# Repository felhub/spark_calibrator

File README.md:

# spark_calibrator
## Be carefull! Igntion coils can step up the voltage up to 1:100, wich means on the secondary side there can be voltages up to 40kV!
Over serial communication controlled spark generator using an arduino as digital controller and a car ignition coil as step up transformer.  
A 3D modell of the full assembly and spark gab, as well as all 3d printed parts will be added soon.

## Schematics (without Arduino)
A MOSFET is used to switch the coil. To avoid voltage spikes on the direct switching action, C2 is used to buffer the spike.  
To limit the overall voltage spike on the primary side, the TVS-diode D2 is used to limit to 440V.  

Switching and digital side are isolated via an optocoupler

## Simulation

In blue one can see the input pwm signal, triggering the charge of the coil, seen in the current over the coil in red. After voltage to the coil is cut of, the magnetic field collapses with a huge voltage spike in green. The spike is limited by the TVS-diode to 440V, this can be seen as clipping on the green signal.

## Board layout
The board can be screwed directly to the coil terminals, to keep the leads as short as possible, depending on your could the board has to be adjusted.  
The Arduino is mounted via a 3D printed part on the back of the coil and connects to the board via 3 wires.  

| main_board | ignition coil |
|:-----------------------------:|:----------------------------------:|
|  |  |

## Spark gap

In order to generate consistent sparks, the spark gap should consist of two pointy metal parts. For spark calibration, audio reflections should be avoided, therefore I build a small spark gap device, using sewing needles and cardboard. The width can be varied, to test the effect of the spark length on the generated impulse.

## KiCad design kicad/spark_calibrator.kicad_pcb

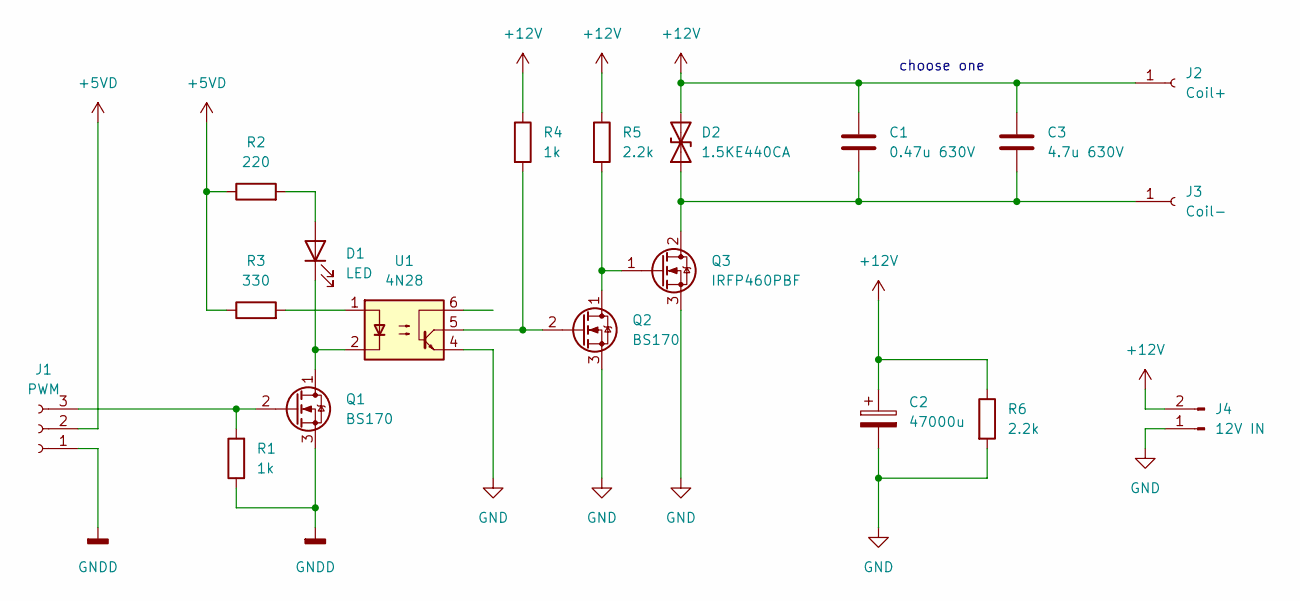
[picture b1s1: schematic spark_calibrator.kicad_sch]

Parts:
C1: 0.47u 630V; C_Rect_L26.5mm_W10.5mm_P22.50mm_MKS4
C2: 47000u; CP_Radial_D35.0mm_P10.00mm_SnapIn
C3: 4.7u 630V; C_Rect_L31.5mm_W17.0mm_P27.50mm_MKS4
D1: LED; LED_D3.0mm
D2: 1.5KE440CA; D_DO-201_P15.24mm_Horizontal
J1: PWM; PinHeader_1x03_P2.54mm_Horizontal
J2: Coil+; MountingHole_6.4mm_M6_Pad
J3: Coil-; MountingHole_5.3mm_M5_Pad
J4: 12V IN; TerminalBlock_bornier-2_P5.08mm
Q1, Q2: BS170; TO-92_Inline
Q3: IRFP460PBF; TO-247-3_Vertical
R1, R4: 1k; R_Axial_DIN0207_L6.3mm_D2.5mm_P10.16mm_Horizontal
R2: 220; R_Axial_DIN0207_L6.3mm_D2.5mm_P10.16mm_Horizontal
R3: 330; R_Axial_DIN0207_L6.3mm_D2.5mm_P10.16mm_Horizontal
R5, R6: 2.2k; R_Axial_DIN0207_L6.3mm_D2.5mm_P10.16mm_Horizontal
U1: 4N28; DIP-6_W7.62mm

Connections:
+5VD: J1.2, R2.1, R3.1
+12V: C1.1, C2.1, C3.1, D2.2 (A2), J2.1, J4.2, R4.1, R5.1, R6.1
GND: C2.2, J4.1, Q2.3 (S), Q3.3 (S), R6.2, U1.4
GNDD: J1.1, Q1.3 (S), R1.1
unnamed: C1.2, C3.2, D2.1 (A1), J3.1, Q3.2 (D)
unnamed: D1.1 (K), Q1.1 (D), U1.2
unnamed: D1.2 (A), R2.2
unnamed: J1.3, Q1.2 (G), R1.2
unnamed: Q2.1 (D), Q3.1 (G), R5.2
unnamed: Q2.2 (G), R4.2, U1.5
unnamed: R3.2, U1.1

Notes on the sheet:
choose one

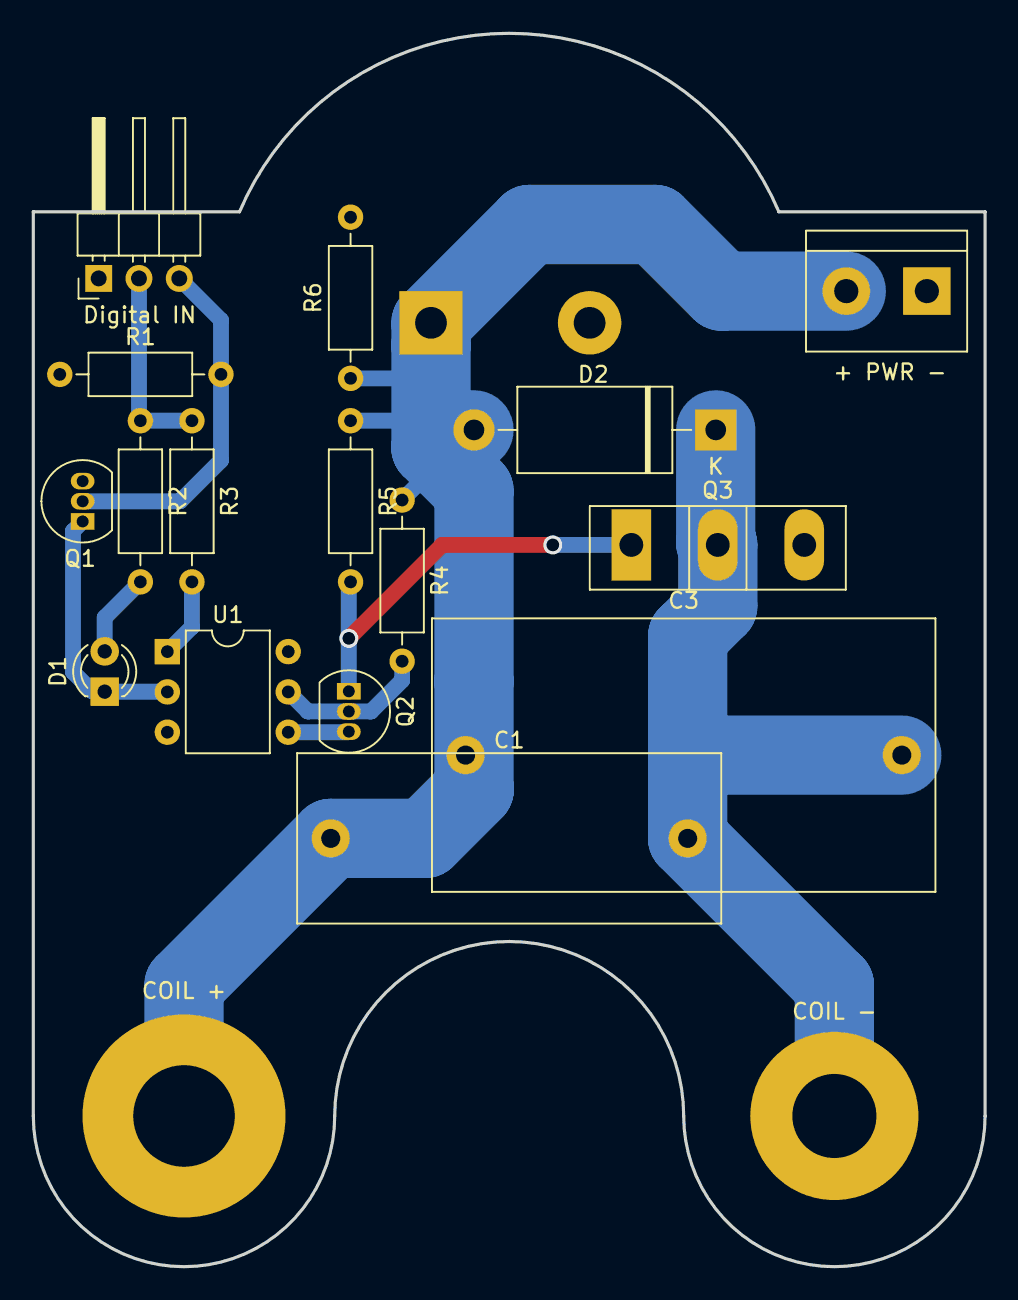
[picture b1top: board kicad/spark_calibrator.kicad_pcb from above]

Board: 2 copper layers, 60.0 x 77.8 mm, 19 parts (1 on the bottom side), 11 nets.

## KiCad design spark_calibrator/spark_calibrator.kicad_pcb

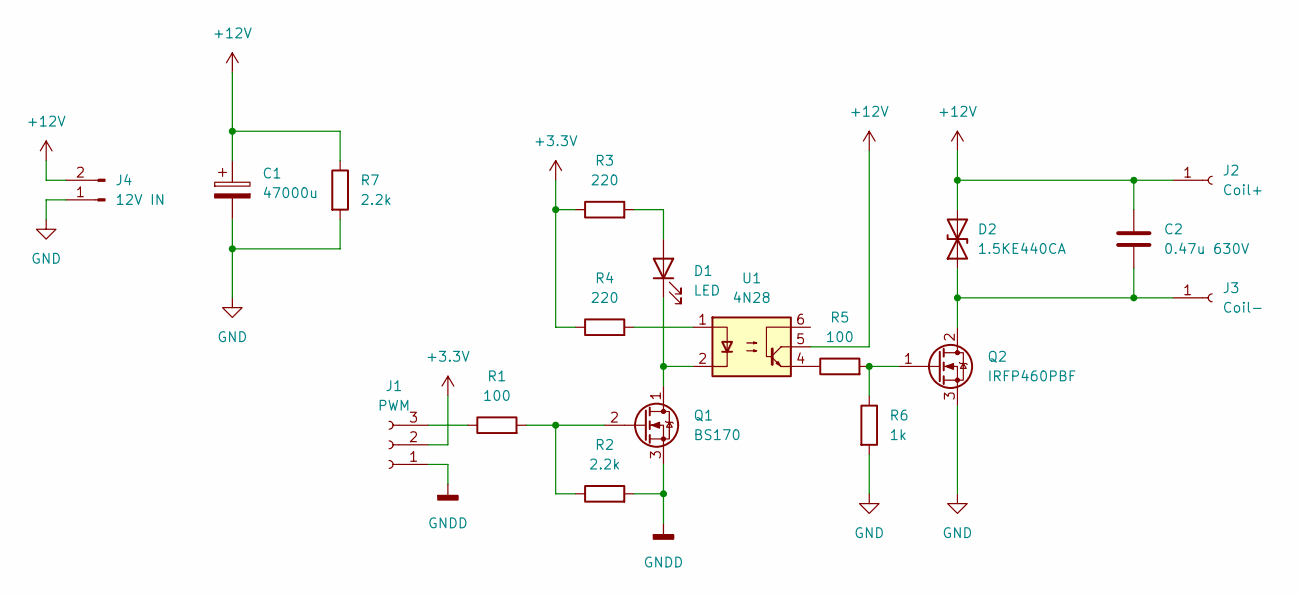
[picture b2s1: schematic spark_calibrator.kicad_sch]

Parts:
C1: 47000u; CP_Radial_D35.0mm_P10.00mm_SnapIn
C2: 0.47u 630V; C_Rect_L26.5mm_W10.5mm_P22.50mm_MKS4
D1: LED; LED_D3.0mm
D2: 1.5KE440CA; D_DO-201_P15.24mm_Horizontal
J1: PWM; PinHeader_1x03_P2.54mm_Horizontal
J2: Coil+; MountingHole_6.4mm_M6_Pad
J3: Coil-; MountingHole_5.3mm_M5_Pad
J4: 12V IN; TerminalBlock_bornier-2_P5.08mm
Q1: BS170; TO-92_Inline
Q2: IRFP460PBF; TO-247-3_Vertical
R1, R5: 100; R_Axial_DIN0207_L6.3mm_D2.5mm_P10.16mm_Horizontal
R2, R7: 2.2k; R_Axial_DIN0207_L6.3mm_D2.5mm_P10.16mm_Horizontal
R3, R4: 220; R_Axial_DIN0207_L6.3mm_D2.5mm_P10.16mm_Horizontal
R6: 1k; R_Axial_DIN0207_L6.3mm_D2.5mm_P10.16mm_Horizontal
U1: 4N28; DIP-6_W7.62mm

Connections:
+3V3: J1.2, R3.1, R4.1
+12V: C1.1, C2.1, D2.2 (A2), J2.1, J4.2, R7.1, U1.5
GND: C1.2, J4.1, Q2.3 (S), R6.2, R7.2
GNDD: J1.1, Q1.3 (S), R2.2
unnamed: C2.2, D2.1 (A1), J3.1, Q2.2 (D)
unnamed: D1.1 (K), Q1.1 (D), U1.2
unnamed: D1.2 (A), R3.2
unnamed: J1.3, R1.1
unnamed: Q1.2 (G), R1.2, R2.1
unnamed: Q2.1 (G), R5.2, R6.1
unnamed: R4.2, U1.1
unnamed: R5.1, U1.4

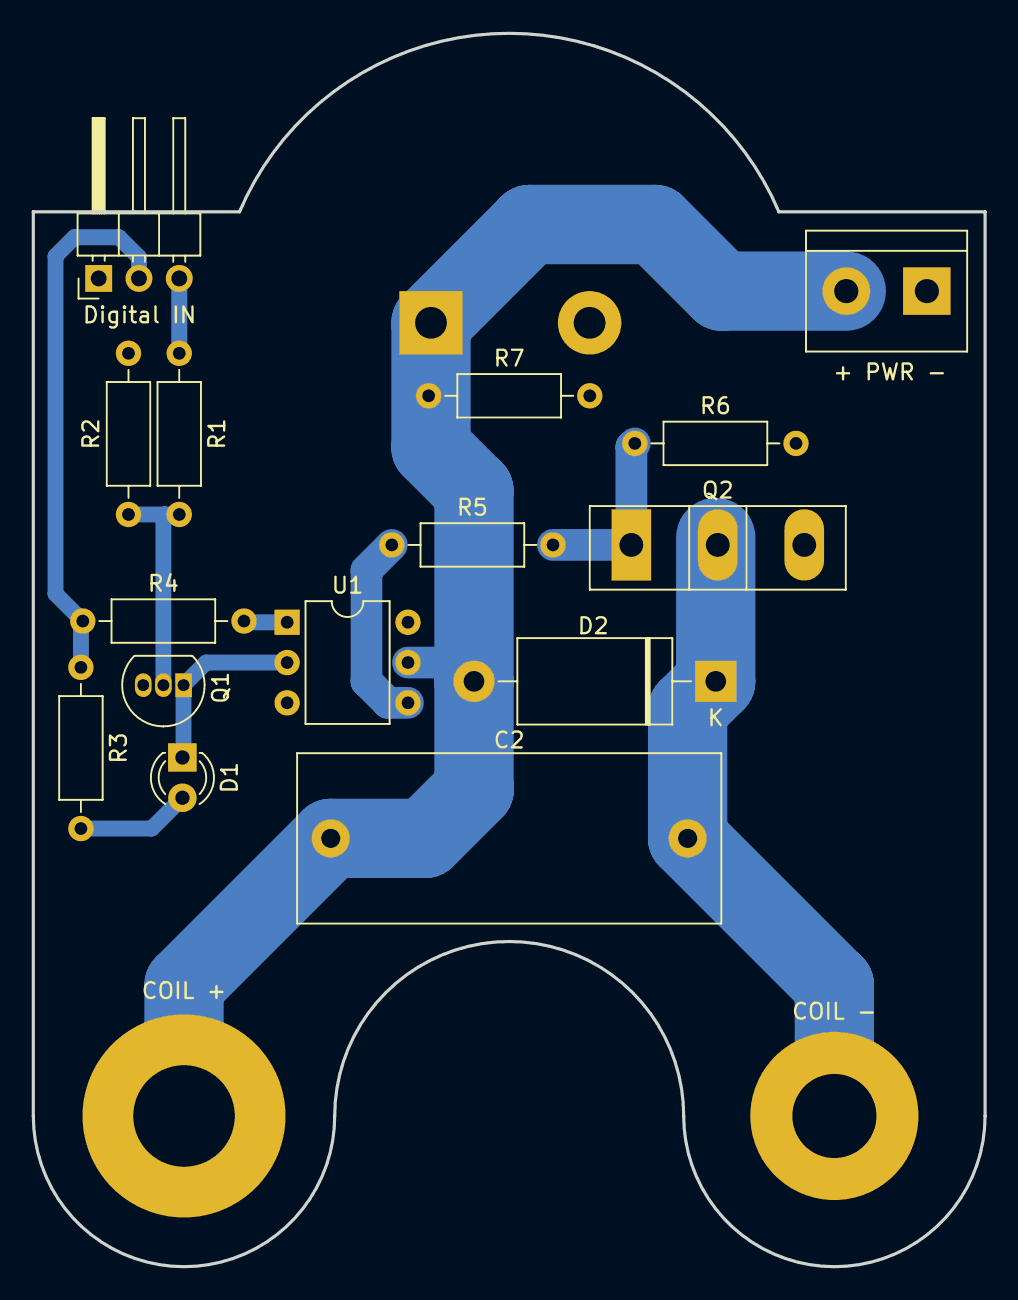
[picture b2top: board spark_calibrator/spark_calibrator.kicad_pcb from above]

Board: 2 copper layers, 60.0 x 77.8 mm, 18 parts (1 on the bottom side), 12 nets.

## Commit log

2022-03-07 aestetic updates
2022-03-07 Added warning
2022-03-07 added arduino code
2022-03-10 faster off switching
2022-03-10 new imgs
2022-03-10 added simulation
2022-03-10 added simulation and spark gap
2022-03-12 first prototype
2022-03-14 R4 to 2.2k
